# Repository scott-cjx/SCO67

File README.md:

# SCO67

## For action
### Hardware
Main: <br>
- SW61 is not connected -> Solder jumper from D50 to D61
- D41 & D65 (COL 14) not connected (not accounted for) -> Solder new connection to carrier board.
- Capslock (SW29) is out of place.

Daughter Board: <br>
- Connections on WEACT PI PICO RP2040 is incorrectly reflected to headers in kicad

### Software
- microcontroller does not start immediately on boot. 
    - reviewed and solved temporarly by mounting device in boot.py
- Found limitation that there is max 6kro (6 Key Roll Over) not NKRO!!

Layers are not implemented fully
Multikey actions are not implemented fully

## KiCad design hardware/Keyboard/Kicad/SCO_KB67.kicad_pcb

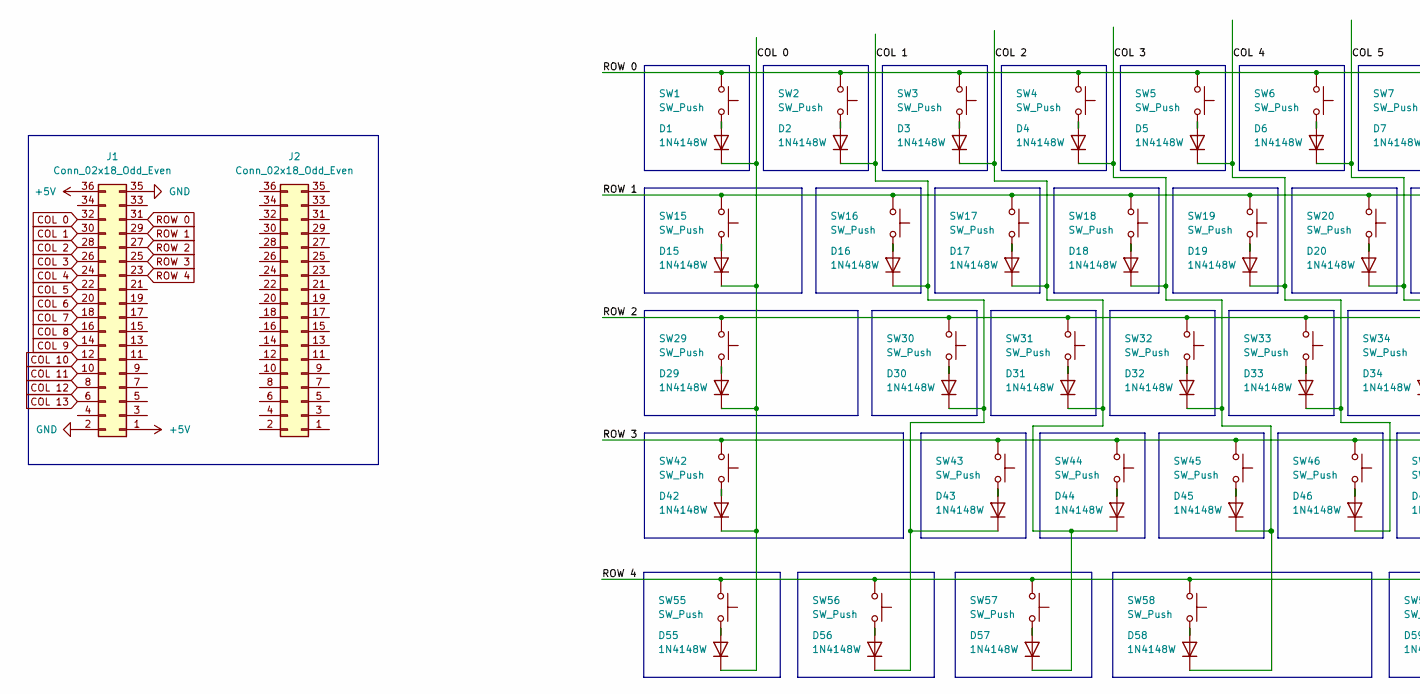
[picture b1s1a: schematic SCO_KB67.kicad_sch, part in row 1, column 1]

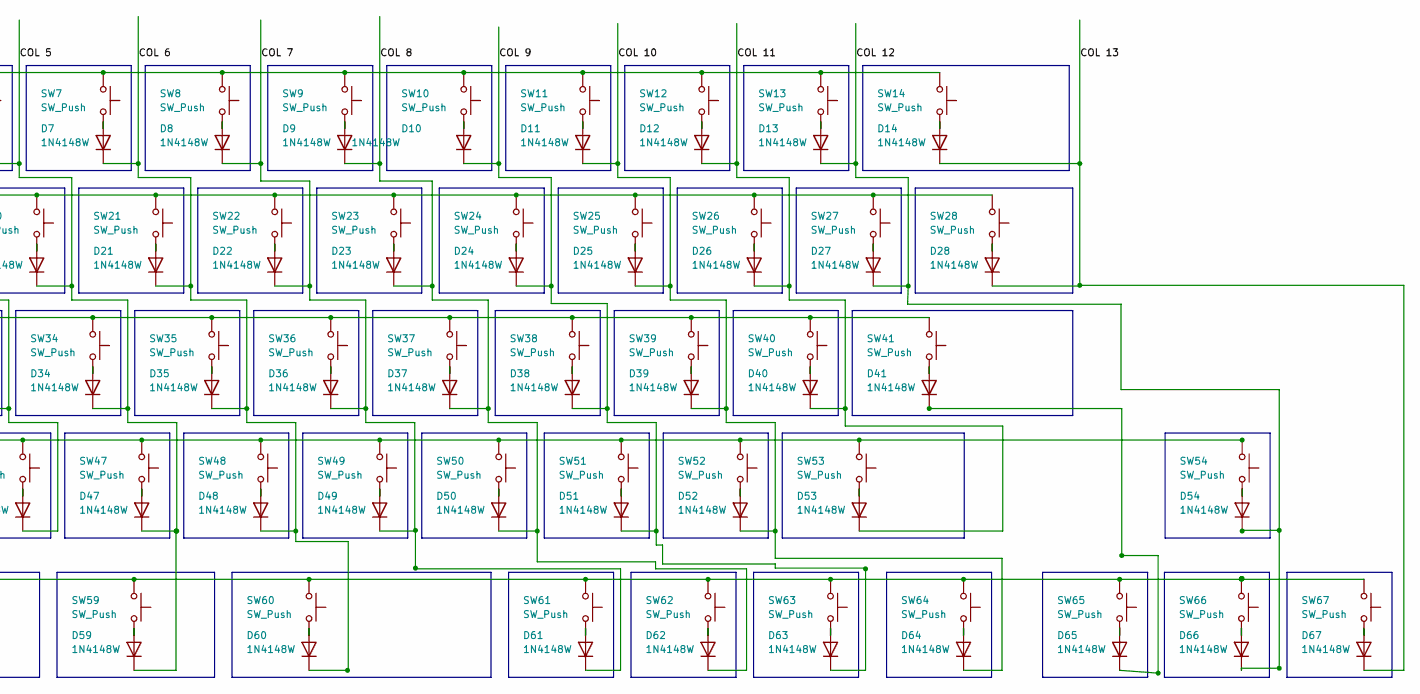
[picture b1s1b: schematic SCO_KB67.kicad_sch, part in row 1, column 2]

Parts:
D1, D2, D3, D4, D5, D6, D7, D8, D9, D10, D11, D12, D13, D14, D15, D16, D17, D18, D19, D20, D21, D22, D23, D24, D25, D26, D27, D28, D29, D30, D31, D32, D33, D34, D35, D36, D37, D38, D39, D40, D41, D42, D43, D44, D45, D46, D47, D48, D49, D50, D51, D52, D53, D54, D55, D56, D57, D58, D59, D60, D61, D62, D63, D64, D65, D66, D67: 1N4148W; D_SOD-123
J1, J2: Conn_02x18_Odd_Even; PinHeader_2x18_P2.54mm_Vertical
SW1, SW2, SW3, SW4, SW5, SW6, SW7, SW8, SW9, SW10, SW11, SW12, SW13, SW14, SW15, SW16, SW17, SW18, SW19, SW20, SW21, SW22, SW23, SW24, SW25, SW26, SW27, SW28, SW29, SW30, SW31, SW32, SW33, SW34, SW35, SW36, SW37, SW38, SW39, SW40, SW41, SW42, SW43, SW44, SW45, SW46, SW47, SW48, SW49, SW50, SW51, SW52, SW53, SW54, SW55, SW56, SW57, SW58, SW59, SW60, SW61, SW62, SW63, SW64, SW65, SW66, SW67: SW_Push; SW_MX

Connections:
COL 0: D1.1 (K), D15.1 (K), D29.1 (K), D42.1 (K), D55.1 (K); also elsewhere on the board
COL 1: D2.1 (K), D16.1 (K), D30.1 (K), D43.1 (K), D56.1 (K); also elsewhere on the board
COL 2: D3.1 (K), D17.1 (K), D31.1 (K), D44.1 (K), D57.1 (K); also elsewhere on the board
COL 3: D4.1 (K), D18.1 (K), D32.1 (K), D45.1 (K), D58.1 (K); also elsewhere on the board
COL 4: D5.1 (K), D19.1 (K), D33.1 (K), D46.1 (K); also elsewhere on the board
COL 5: D6.1 (K), D20.1 (K), D34.1 (K), D47.1 (K), D59.1 (K); also elsewhere on the board
COL 6: D7.1 (K), D21.1 (K), D35.1 (K), D48.1 (K), D60.1 (K); also elsewhere on the board
COL 7: D8.1 (K), D22.1 (K), D36.1 (K), D49.1 (K); also elsewhere on the board
COL 8: D9.1 (K), D23.1 (K), D37.1 (K), D50.1 (K), D62.1 (K); also elsewhere on the board
COL 9: D10.1 (K), D24.1 (K), D38.1 (K), D51.1 (K), D63.1 (K); also elsewhere on the board
COL 10: D11.1 (K), D25.1 (K), D39.1 (K), D52.1 (K), D64.1 (K); also elsewhere on the board
COL 11: D12.1 (K), D26.1 (K), D40.1 (K), D53.1 (K); also elsewhere on the board
COL 12: D13.1 (K), D27.1 (K), D54.1 (K), D66.1 (K); also elsewhere on the board
COL 13: D14.1 (K), D28.1 (K), D67.1 (K); also elsewhere on the board
unnamed: D1.2 (A), SW1.2
unnamed: D2.2 (A), SW2.2
unnamed: D3.2 (A), SW3.2
unnamed: D4.2 (A), SW4.2
unnamed: D5.2 (A), SW5.2
unnamed: D6.2 (A), SW6.2
unnamed: D7.2 (A), SW7.2
unnamed: D8.2 (A), SW8.2
unnamed: D9.2 (A), SW9.2
unnamed: D10.2 (A), SW10.2
unnamed: D11.2 (A), SW11.2
unnamed: D12.2 (A), SW12.2
unnamed: D13.2 (A), SW13.2
unnamed: D14.2 (A), SW14.2
unnamed: D15.2 (A), SW15.2
unnamed: D16.2 (A), SW16.2
unnamed: D17.2 (A), SW17.2
unnamed: D18.2 (A), SW18.2
unnamed: D19.2 (A), SW19.2
unnamed: D20.2 (A), SW20.2
unnamed: D21.2 (A), SW21.2
unnamed: D22.2 (A), SW22.2
unnamed: D23.2 (A), SW23.2
unnamed: D24.2 (A), SW24.2
unnamed: D25.2 (A), SW25.2
unnamed: D26.2 (A), SW26.2
unnamed: D27.2 (A), SW27.2
unnamed: D28.2 (A), SW28.2
unnamed: D29.2 (A), SW29.2
unnamed: D30.2 (A), SW30.2
unnamed: D31.2 (A), SW31.2
unnamed: D32.2 (A), SW32.2
unnamed: D33.2 (A), SW33.2
unnamed: D34.2 (A), SW34.2
unnamed: D35.2 (A), SW35.2
unnamed: D36.2 (A), SW36.2
unnamed: D37.2 (A), SW37.2
unnamed: D38.2 (A), SW38.2
unnamed: D39.2 (A), SW39.2
unnamed: D40.2 (A), SW40.2
unnamed: D41.2 (A), SW41.2
unnamed: D42.2 (A), SW42.2
unnamed: D43.2 (A), SW43.2
unnamed: D44.2 (A), SW44.2
unnamed: D45.2 (A), SW45.2
unnamed: D46.2 (A), SW46.2
unnamed: D47.2 (A), SW47.2
unnamed: D48.2 (A), SW48.2
unnamed: D49.2 (A), SW49.2
unnamed: D50.2 (A), SW50.2
unnamed: D51.2 (A), SW51.2
unnamed: D52.2 (A), SW52.2
unnamed: D53.2 (A), SW53.2
unnamed: D54.2 (A), SW54.2
unnamed: D55.2 (A), SW55.2
unnamed: D56.2 (A), SW56.2
unnamed: D57.2 (A), SW57.2
unnamed: D58.2 (A), SW58.2
unnamed: D59.2 (A), SW59.2
unnamed: D60.2 (A), SW60.2
unnamed: D61.2 (A), SW61.2
unnamed: D62.2 (A), SW62.2
unnamed: D63.2 (A), SW63.2
unnamed: D64.2 (A), SW64.2
unnamed: D41.1 (K), D65.1 (K)
unnamed: D65.2 (A), SW65.2
unnamed: D66.2 (A), SW66.2
unnamed: D67.2 (A), SW67.2
unnamed: J1.1, J1.36
unnamed: J1.2, J1.35
ROW 0: SW1.1, SW2.1, SW3.1, SW4.1, SW5.1, SW6.1, SW7.1, SW8.1, SW9.1, SW10.1, SW11.1, SW12.1, SW13.1, SW14.1; also elsewhere on the board
ROW 1: SW15.1, SW16.1, SW17.1, SW18.1, SW19.1, SW20.1, SW21.1, SW22.1, SW23.1, SW24.1, SW25.1, SW26.1, SW27.1, SW28.1; also elsewhere on the board
ROW 2: SW29.1, SW30.1, SW31.1, SW32.1, SW33.1, SW34.1, SW35.1, SW36.1, SW37.1, SW38.1, SW39.1, SW40.1, SW41.1; also elsewhere on the board
ROW 3: SW42.1, SW43.1, SW44.1, SW45.1, SW46.1, SW47.1, SW48.1, SW49.1, SW50.1, SW51.1, SW52.1, SW53.1, SW54.1; also elsewhere on the board
ROW 4: SW55.1, SW56.1, SW57.1, SW58.1, SW59.1, SW60.1, SW61.1, SW62.1, SW63.1, SW64.1, SW65.1, SW66.1, SW67.1; also elsewhere on the board

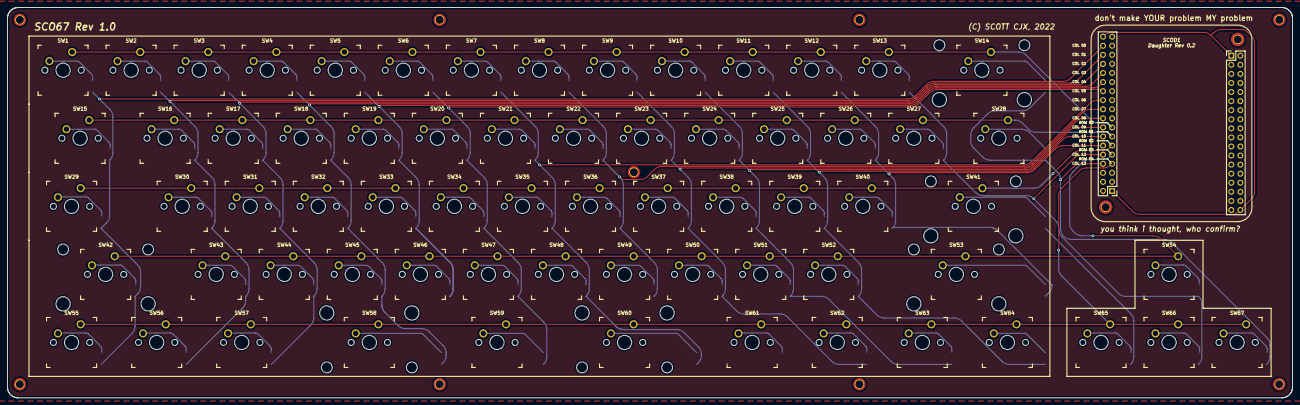
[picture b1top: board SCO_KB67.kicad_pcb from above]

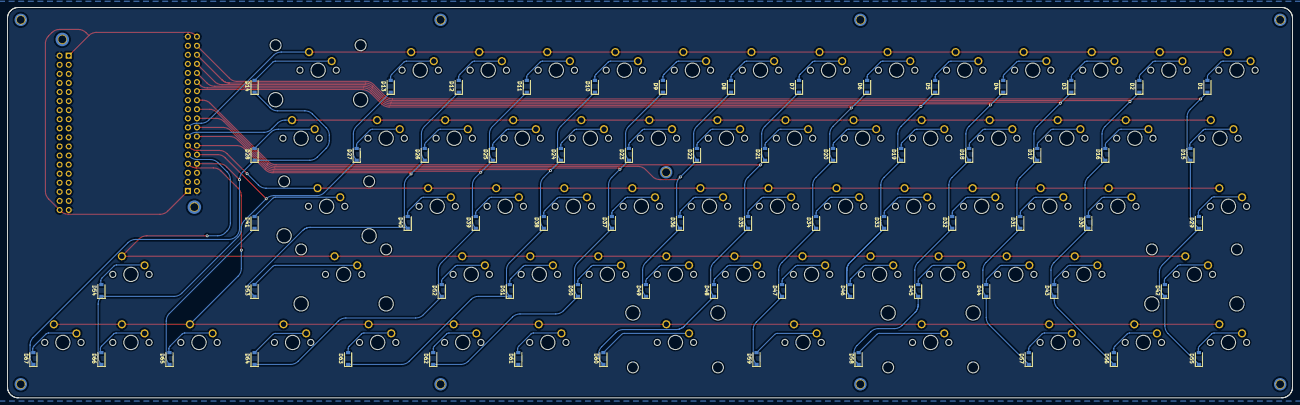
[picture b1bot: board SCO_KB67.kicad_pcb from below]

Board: 2 copper layers, 359.7 x 109.3 mm, 150 parts (67 on the bottom side), 89 nets.

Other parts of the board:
MH1, MH2, MH3, MH4, MH5, MH6, MH7, MH8, MH9: MountingHole_2.2mm_M2_ISO7380_Pad_TopBottom
SCOD1: Daughter Rev 0.2
STAB1, STAB2, STAB3, STAB4, STAB5, STAB6: Stabilizer_MX_2u

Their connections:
+5V: SCOD1.1, SCOD1.36
COL 0: SCOD1.34; also elsewhere on the board
COL 1: SCOD1.32; also elsewhere on the board
COL 2: SCOD1.30; also elsewhere on the board
COL 3: SCOD1.28; also elsewhere on the board
COL 4: SCOD1.26; also elsewhere on the board
COL 5: SCOD1.24; also elsewhere on the board
COL 6: SCOD1.22; also elsewhere on the board
COL 7: SCOD1.20; also elsewhere on the board
COL 8: SCOD1.18; also elsewhere on the board
COL 9: SCOD1.16; also elsewhere on the board
COL 10: SCOD1.14; also elsewhere on the board
COL 11: SCOD1.12; also elsewhere on the board
COL 12: SCOD1.10; also elsewhere on the board
COL 13: SCOD1.8; also elsewhere on the board
GND: SCOD1.2, SCOD1.35
ROW 0: SCOD1.15; also elsewhere on the board
ROW 1: SCOD1.13; also elsewhere on the board
ROW 2: SCOD1.11; also elsewhere on the board
ROW 3: SCOD1.9; also elsewhere on the board
ROW 4: SCOD1.7; also elsewhere on the board

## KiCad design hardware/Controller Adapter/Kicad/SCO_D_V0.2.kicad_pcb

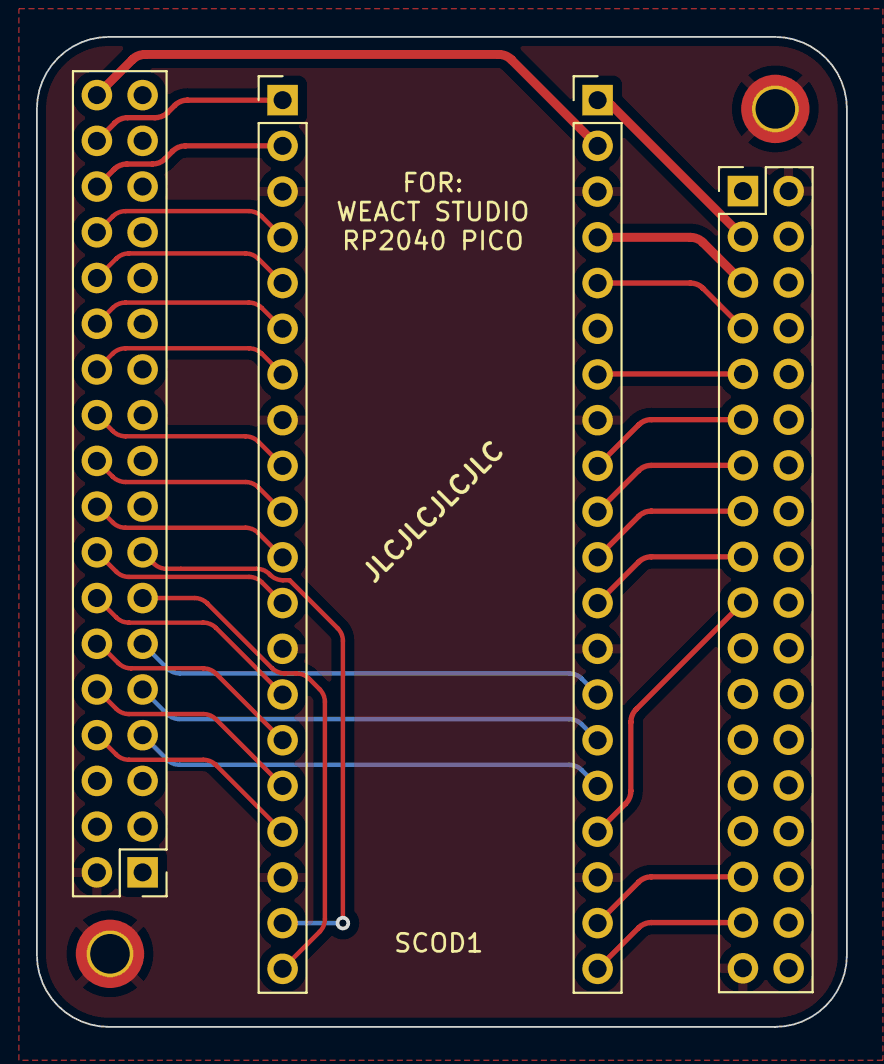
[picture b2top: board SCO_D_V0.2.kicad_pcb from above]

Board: 2 copper layers, 45.0 x 55.0 mm, 3 parts (0 on the bottom side), 32 nets.

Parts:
J1, J2: Conn_01x20; PinHeader_1x20_P2.54mm_Vertical
SCOD1: Daughter Rev 0.2

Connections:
+3V3: J2.4, SCOD1.5
GND: J1.3, J1.8, J1.13, J1.18, J2.3, J2.8, J2.13, J2.18, SCOD1.1, SCOD1.2, SCOD1.35
IO 0: J1.1, SCOD1.34
IO 1: J1.2, SCOD1.32
IO 2: J1.4, SCOD1.30
IO 3: J1.5, SCOD1.28
IO 4: J1.6, SCOD1.26
IO 5: J1.7, SCOD1.24
IO 6: J1.9, SCOD1.22
IO 7: J1.10, SCOD1.20
IO 8: J1.11, SCOD1.18
IO 9: J1.12, SCOD1.16
IO 10: J1.14, SCOD1.14
IO 11: J1.15, SCOD1.12
IO 12: J1.16, SCOD1.10
IO 13: J1.17, SCOD1.8
IO 14: J1.19, SCOD1.15
IO 15: J1.20, SCOD1.13
IO 16: J2.14, SCOD1.11
IO 17: J2.15, SCOD1.9
IO 18: J2.16, SCOD1.7
IO 19: J2.17, SCOD1.19
IO 20: J2.5, SCOD1.7
IO 21: J2.7, SCOD1.9
IO 22: J2.9, SCOD1.11
IO 23: J2.12, SCOD1.17
SCL 0: J2.10, SCOD1.13
SDA 0: J2.11, SCOD1.15
UART0 RX: J2.19, SCOD1.31
UART0 TX: J2.20, SCOD1.33
VBUS: J2.1, SCOD1.3
VCC: J2.2, SCOD1.36

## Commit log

2022-06-20 Added v0.0.1
2022-06-21 Added fab files for SCO67
